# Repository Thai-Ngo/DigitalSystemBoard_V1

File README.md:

# digitalSystemBoard
Project design digital system board

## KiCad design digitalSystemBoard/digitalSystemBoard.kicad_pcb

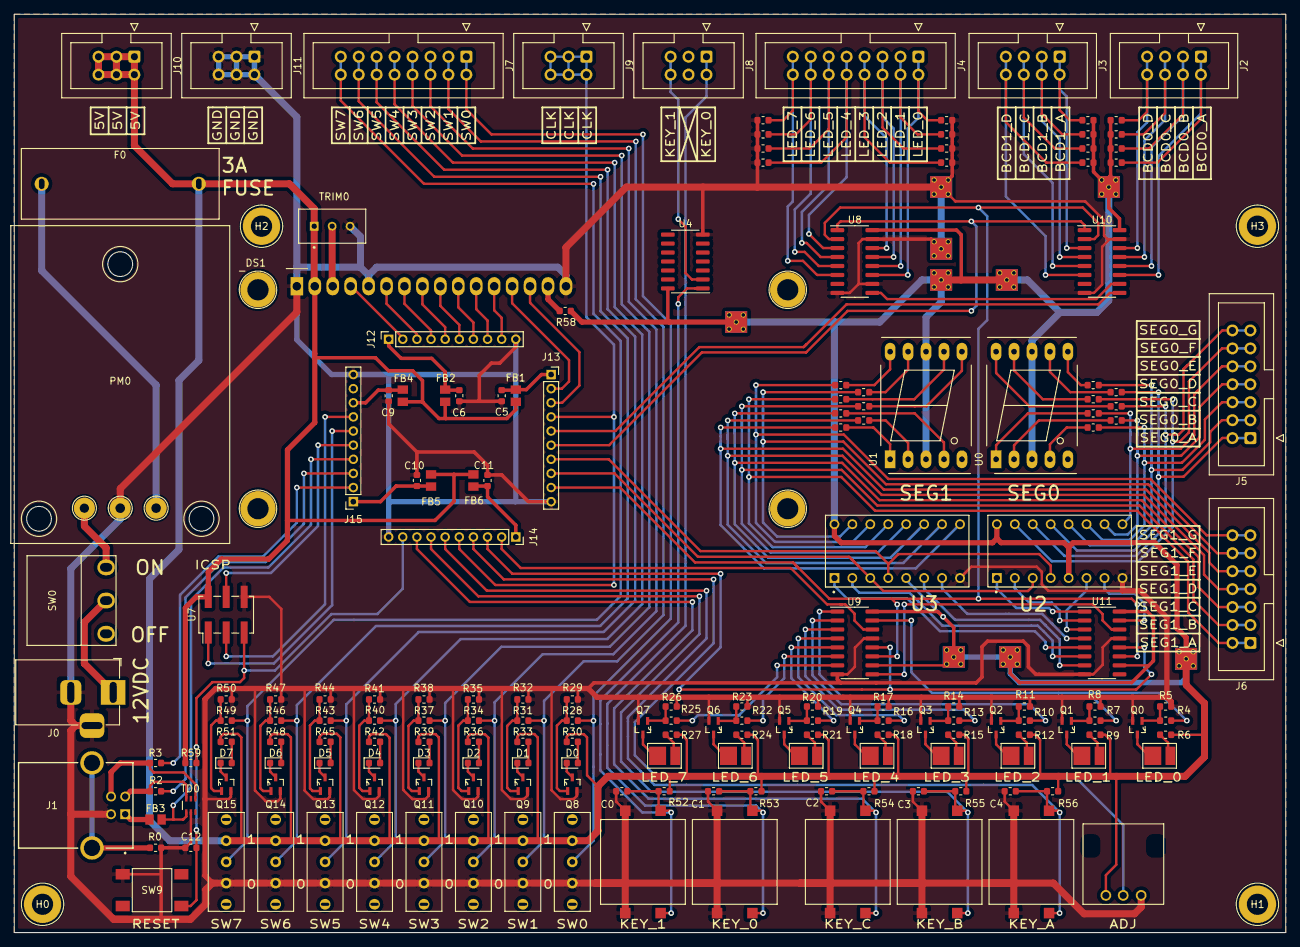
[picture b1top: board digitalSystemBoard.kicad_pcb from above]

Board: 2 copper layers, 180.0 x 130.0 mm, 188 parts (0 on the bottom side), 166 nets.

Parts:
C0, C1, C2, C3, C4, C5, C6, C9, C10, C11, C12: 0.1uF; C_0603_1608Metric
D0, D1, D2, D3, D4, D5, D6, D7: LED; LED_0603_1608Metric
DS1: WC1602A
F0: 3A; Fuse
FB1, FB2, FB3, FB4, FB5, FB6: 80Ohm; FerriteBead
H0, H1, H2, H3: MountingHole; Mountinghole_M3
J0: Barrel_Jack; BarrelJack_Horizontal
J1: USB-B; SAMTEC_USB-B-S-X-X-TH-TR
J2, J3: Conn_02x04_Odd_Even; IDC-Header_2x04_P2.54mm_Vertical
J4, J7: Conn_02x08_Odd_Even; IDC-Header_2x08_P2.54mm_Vertical
J5, J6: Conn_02x07_Odd_Even; IDC-Header_2x07_P2.54mm_Vertical
J8, J9, J10, J11: Conn_02x03_Odd_Even; IDC-Header_2x03_P2.54mm_Vertical
J12, J13, J14, J15: Conn_01x10_Female; PinSocket_1x10_P2.00mm_Vertical
KEY0, KEY1, KEY2, KEY3, KEY4: ButtonFirst; Button
LED0, LED1, LED2, LED3, LED4, LED5, LED6, LED7: LED; LED_3528
PM0: Power_Module
Q0, Q1, Q2, Q3, Q4, Q5, Q6, Q7, Q8, Q9, Q10, Q11, Q12, Q13, Q14, Q15: BC847; SO65P210X100-3N
R0, R2, R3: 22; R_0603_1608Metric
R4, R7, R10, R13, R16, R19, R22, R25: 15k; R_0603_1608Metric
R5, R6, R8, R9, R11, R12, R14, R15, R17, R18, R20, R21, R23, R24, R26, R27: 2.49k; R_0603_1608Metric
R28, R31, R34, R37, R40, R43, R46, R49: 27k; R_0603_1608Metric
R29, R32, R35, R38, R41, R44, R47, R50: 4.7k; R_0603_1608Metric
R30, R33, R36, R39, R42, R45, R48, R51: 1.8k; R_0603_1608Metric
R52, R53, R54, R55, R56, R59, R82, R83, R84, R85, R86, R87, R88, R89: 10k; R_0603_1608Metric
R58: 220; R_0603_1608Metric
R60, R61, R62, R63, R64, R65, R66, R67, R68, R69, R70, R71, R72, R73: 330; R_0603_1608Metric
R74, R75, R76, R77, R78, R79, R80, R81: 47k; R_0603_1608Metric
SW0: SW_SPDT; SS-12D11
SW1, SW2, SW3, SW4, SW5, SW6, SW7, SW8: IO_Switch; SS-12F44G5
SW9: ButtonFirst; Button_CLOCK
TD0: SMF05C.TCT; SC70-6
TRIM0: Potentiometer; TRIM_3296W-1-501
U0, U1: KCSA02-105; 7SegmentLED_LTS6760_LTS6780
U2, U3: 74LS47; DIP_16_PIN_SOCKET
U4: 74LS04; SOIC-14_3.9x8.7mm_P1.27mm
U5: Potentiometer; RV09S
U7: ICSP; PinHeader_2x03_P2.54mm_Vertical_SMD
U8, U10: 74HC165; SOIC-16_3.9x9.9mm_P1.27mm
U9, U11: 74HC595; SOIC-16_3.9x9.9mm_P1.27mm

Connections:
/7SEGLED_TEST_OFF: J13.7, U2.4, U3.4
/7SEGLED_TEST_ON: J13.8, U2.3, U3.3
/ADJ_CLOCK: J14.4, U5.2
/BCD_A_0: U2.7, U11.15
/BCD_A_1: U3.7, U11.4
/BCD_B_0: U2.1, U11.1
/BCD_B_1: U3.1, U11.5
/BCD_C_0: U2.2, U11.2
/BCD_C_1: U3.2, U11.6
/BCD_D_0: U2.6, U11.3
/BCD_D_1: U3.6, U11.7
/CHANGE_CLK_SRC: C4.1, J14.6, KEY4.2, KEY4.3, R56.1
/CLK_OUT: J9.1, J9.2, J9.3, J9.4, J9.5, J9.6, J13.4, J14.5
/DOWN_CLOCK: C3.2, J14.7, KEY3.2, KEY3.3, R55.1
/GPIO_BCD_A_0: J2.1, J2.2, R82.2, U10.11
/GPIO_BCD_A_1: J3.1, J3.2, R86.2, U10.3
/GPIO_BCD_B_0: J2.3, J2.4, R83.2, U10.12
/GPIO_BCD_B_1: J3.3, J3.4, R87.2, U10.4
/GPIO_BCD_C_0: J2.5, J2.6, R84.2, U10.13
/GPIO_BCD_C_1: J3.5, J3.6, R88.2, U10.5
/GPIO_BCD_D_0: J2.7, J2.8, R85.2, U10.14
/GPIO_BCD_D_1: J3.7, J3.8, R89.2, U10.6
/GPIO_LED_1: J4.1, J4.2, R74.2, U8.11
/GPIO_LED_2: J4.3, J4.4, R75.2, U8.12
/GPIO_LED_3: J4.5, J4.6, R76.2, U8.13
/GPIO_LED_4: J4.7, J4.8, R77.2, U8.14
/GPIO_LED_5: J4.9, J4.10, R78.2, U8.3
/GPIO_LED_6: J4.11, J4.12, R79.2, U8.4
/GPIO_LED_7: J4.13, J4.14, R80.2, U8.5
/GPIO_LED_8: J4.15, J4.16, R81.2, U8.6
/KEY0: C1.1, J8.1, J8.2, KEY0.2, KEY0.3, R53.1
/KEY1: J8.5, J8.6, U4.2
/LED1: R4.2, U9.15
/LED2: R7.2, U9.1
/LED3: R10.2, U9.2
/LED4: R13.2, U9.3
/LED5: R16.2, U9.4
/LED6: R19.2, U9.5
/LED7: R22.2, U9.6
/LED8: R25.2, U9.7
/MCU/D+: J15.2, R3.1
/MCU/D-: J15.3, R2.1
/MCU/IC_165_CTRL: J13.6, U8.1, U10.1
/MCU/IC_165_TO_MCU: J13.5, U10.9
/MCU/IC_595_CTRL: J14.3, U9.12, U11.12
/MCU/IC_CLOCK: J13.9, U8.2, U9.11, U10.2, U11.11
/MCU/LCD_0: DS1.7, J12.4
/MCU/LCD_1: DS1.8, J12.5
/MCU/LCD_2: DS1.9, J12.6
/MCU/LCD_3: DS1.10, J12.7
/MCU/LCD_4: DS1.11, J12.8
/MCU/LCD_5: DS1.12, J12.9
/MCU/LCD_6: DS1.13, J13.2
/MCU/LCD_7: DS1.14, J13.3
/MCU/LCD_ENABLE: DS1.6, J12.3
/MCU/LCD_RS: DS1.4, J12.2
/MCU/MCU_TO_IC_595: J14.2, U9.14
/MCU/MISO: J15.6, U7.1
/MCU/MOSI: J15.5, U7.4
/MCU/RESET: C12.1, J14.9, R59.2, SW9.1, U7.5
/MCU/SCK: J15.7, U7.3
/MCU/VBUS: FB3.1, J15.4, TD0.1
/MCU/VCC_0: C6.1, FB2.2, J12.1
/MCU/VCC_1: C5.1, FB1.2, J13.1
/MCU/VCC_2: C11.1, FB6.2, J14.1
/MCU/VCC_3: C10.1, FB5.2, J15.1
/MCU/VCC_4: C9.1, FB4.2, J15.8
/SEG_A_0: J5.1, J5.2, R60.2, U2.13
/SEG_A_1: J6.1, J6.2, R67.2, U3.13
/SEG_B_0: J5.3, J5.4, R61.2, U2.12
/SEG_B_1: J6.3, J6.4, R68.2, U3.12
/SEG_C_0: J5.5, J5.6, R62.2, U2.11
/SEG_C_1: J6.5, J6.6, R69.2, U3.11
/SEG_D_0: J5.7, J5.8, R63.2, U2.10
/SEG_D_1: J6.7, J6.8, R70.2, U3.10
/SEG_E_0: J5.9, J5.10, R64.2, U2.9
/SEG_E_1: J6.9, J6.10, R71.2, U3.9
/SEG_F_0: J5.11, J5.12, R65.2, U2.15
/SEG_F_1: J6.11, J6.12, R72.2, U3.15
/SEG_G_0: J5.13, J5.14, R66.2, U2.14
/SEG_G_1: J6.13, J6.14, R73.2, U3.14
/SW1: J7.1, J7.2, R28.2, SW1.2
/SW2: J7.3, J7.4, R31.2, SW2.2
/SW3: J7.5, J7.6, R34.2, SW3.2
/SW4: J7.7, J7.8, R37.2, SW4.2
/SW5: J7.9, J7.10, R40.2, SW5.2
/SW6: J7.11, J7.12, R43.2, SW6.2
/SW7: J7.13, J7.14, R46.2, SW7.2
/SW8: J7.15, J7.16, R49.2, SW8.2
/UP_CLOCK: C2.1, J14.8, KEY2.2, KEY2.3, R54.1
/VCC5V: DS1.2, F0.1, FB1.1, FB2.1, FB4.1, FB5.1, FB6.1, J10.1, J10.2, J10.3, J10.4, J10.5, J10.6, R6.1, R9.1, R12.1, R15.1, R18.1, R21.1, R24.1, R27.1, R30.1, R33.1, R36.1, R39.1, R42.1, R45.1, R48.1, R51.1, R52.2, R53.2, R54.2, R55.2, R56.2, R58.2, R59.1, R82.1, R83.1, R84.1, R85.1, R86.1, R87.1, R88.1, R89.1, SW1.1, SW2.1, SW3.1, SW4.1, SW5.1, SW6.1, SW7.1, SW8.1, TRIM0.1, U0.3, U0.8, U1.3, U1.8, U2.5, U2.16, U3.5, U3.16, U4.14, U5.1, U7.2, U8.16, U9.10, U9.16, U10.16, U11.10, U11.16
GND: C0.2, C1.2, C2.2, C3.1, C4.2, C5.2, C6.2, C9.2, C10.2, C11.2, C12.2, DS1.1, DS1.5, DS1.16, J0.2, J0.3, J1.4, J11.1, J11.2, J11.3, J11.4, J11.5, J11.6, J12.10, J13.10, J14.10, J15.10, KEY0.1, KEY0.4, KEY1.1, KEY1.4, KEY2.1, KEY2.4, KEY3.1, KEY3.4, KEY4.1, KEY4.4, PM0.2, Q0.2, Q1.2, Q2.2, Q3.2, Q4.2, Q5.2, Q6.2, Q7.2, Q8.2, Q9.2, Q10.2, Q11.2, Q12.2, Q13.2, Q14.2, Q15.2, R0.1, R5.1, R8.1, R11.1, R14.1, R17.1, R20.1, R23.1, R26.1, R29.1, R32.1, R35.1, R38.1, R41.1, R44.1, R47.1, R50.1, R74.1, R75.1, R76.1, R77.1, R78.1, R79.1, R80.1, R81.1, SW1.3, SW2.3, SW3.3, SW4.3, SW5.3, SW6.3, SW7.3, SW8.3, SW9.3, TD0.2, TRIM0.3, U2.8, U3.8, U4.7, U5.3, U7.6, U8.8, U8.10, U8.15, U9.8, U9.13, U10.8, U10.15, U11.8, U11.13
unnamed: C0.1, KEY1.2, KEY1.3, R52.1, U4.1
unnamed: D0.1, Q8.3
unnamed: D0.2, R30.2
unnamed: D1.1, Q9.3
unnamed: D1.2, R33.2
unnamed: D2.1, Q10.3
unnamed: D2.2, R36.2
unnamed: D3.1, Q11.3
unnamed: D3.2, R39.2
unnamed: D4.1, Q12.3
unnamed: D4.2, R42.2
unnamed: D5.1, Q13.3
unnamed: D5.2, R45.2
unnamed: D6.1, Q14.3
unnamed: D6.2, R48.2
unnamed: D7.1, Q15.3
unnamed: D7.2, R51.2
unnamed: DS1.3, TRIM0.2
unnamed: DS1.15, R58.1
unnamed: F0.2, PM0.3
unnamed: FB3.2, J1.1
unnamed: J0.1, SW0.2
unnamed: J1.2, R2.2, TD0.6
unnamed: J1.3, R3.2, TD0.4
unnamed: J1.S1, J1.S2, R0.2
unnamed: LED0.1, Q0.3
unnamed: LED0.2, R6.2
unnamed: LED1.1, Q1.3
unnamed: LED1.2, R9.2
unnamed: LED2.1, Q2.3
unnamed: LED2.2, R12.2
unnamed: LED3.1, Q3.3
unnamed: LED3.2, R15.2
unnamed: LED4.1, Q4.3
unnamed: LED4.2, R18.2
unnamed: LED5.1, Q5.3
unnamed: LED5.2, R21.2
unnamed: LED6.1, Q6.3
unnamed: LED6.2, R24.2
unnamed: LED7.1, Q7.3
unnamed: LED7.2, R27.2
unnamed: PM0.1, SW0.1
unnamed: Q0.1, R4.1, R5.2
unnamed: Q1.1, R7.1, R8.2
unnamed: Q2.1, R10.1, R11.2
unnamed: Q3.1, R13.1, R14.2
unnamed: Q4.1, R16.1, R17.2
unnamed: Q5.1, R19.1, R20.2
unnamed: Q6.1, R22.1, R23.2
unnamed: Q7.1, R25.1, R26.2
unnamed: Q8.1, R28.1, R29.2
unnamed: Q9.1, R31.1, R32.2
unnamed: Q10.1, R34.1, R35.2
unnamed: Q11.1, R37.1, R38.2
unnamed: Q12.1, R40.1, R41.2
unnamed: Q13.1, R43.1, R44.2
unnamed: Q14.1, R46.1, R47.2
unnamed: Q15.1, R49.1, R50.2
unnamed: R60.1, U0.7
unnamed: R61.1, U0.6
unnamed: R62.1, U0.4
unnamed: R63.1, U0.2
unnamed: R64.1, U0.1
unnamed: R65.1, U0.9
unnamed: R66.1, U0.10
unnamed: R67.1, U1.7
unnamed: R68.1, U1.6
unnamed: R69.1, U1.4
unnamed: R70.1, U1.2
unnamed: R71.1, U1.1
unnamed: R72.1, U1.9
unnamed: R73.1, U1.10
unnamed: U8.9, U10.10
unnamed: U9.9, U11.14

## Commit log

2021-06-25 Complete the V1 project
2021-06-27 Edit some track
2021-10-19 Generate BOM, Gerber and CPL file
